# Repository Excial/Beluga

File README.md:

# Beluga
1. Created a sensor board for Beluga robotics platform
2. Contains PCB, Arduino Code

## Project description
A biosensor designed for microbial auditing, which is mounted onboard an autonomous robot as a payload. The PCB in this sensor helps to initiate helps to reduce the streamline the electronics due to space constraints to initiate the sampling sequence / processes of the biosensor.

## Design Objectives
Practice Design objectives in accordance to the IPC-2221 Standard

### V1
[✓] 3.3V LDO

[✓] 12V Buck Converter

[✓] ESP32 Module 

[✓] Bootloader

[✓] Troubleshooting LEDs

[X] Motor Driver LEDs

  - Too bright, need to increase resistance from 1K to 10K.

[✓] Motor Drivers

[X] Circuit Protection

  - Circuit Protection LED mounted wrongly, refer to schematic.
  - Source and Drain of Mosfet is mounted wrongly, needs to be switched.

[✓] M2 Mounting holes

#### Improvements
1. Add a stepper Motor driver
2. Add a buzzer
3. Add a USB Port
4. Add a FDTI chip
5. Increase Resistance for LEDs from 1k to 10K
	5a. Might Remove the LEDs altogether

### V2

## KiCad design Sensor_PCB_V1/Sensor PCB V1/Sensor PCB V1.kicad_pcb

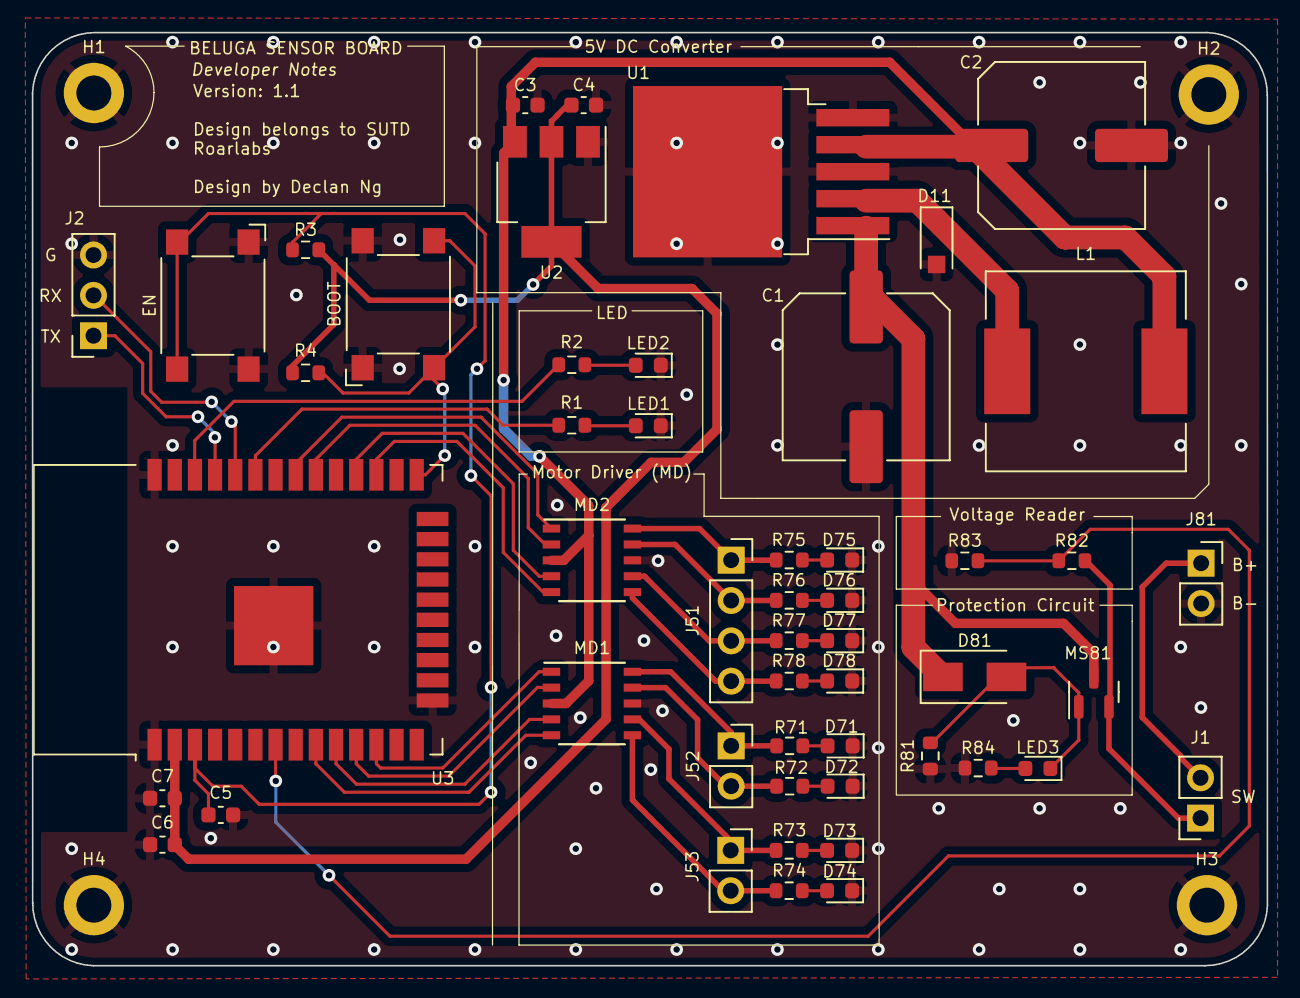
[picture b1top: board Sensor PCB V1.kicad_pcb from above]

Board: 2 copper layers, 77.8 x 58.8 mm, 55 parts (0 on the bottom side), 42 nets.

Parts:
C1: 470uF; C_Elec_10x10.2
C2: 330uF / 35V; C_Elec_10x10.2
C3, C4, C6: 22uF; C_0603_1608Metric
C5: 10uF; C_0603_1608Metric
C7: 0.1uF; C_0603_1608Metric
D11: SK32; D_SOD-123F
D71, D72, D73, D74, D75, D76, D77, D78: LED; LED_0603_1608Metric
D81: SS14; D_SMA
H1, H2, H3, H4: MountingHole_Pad; MountingHole_2.2mm_M2_DIN965_Pad
J1, J81: Conn_01x02_Male; PinSocket_1x02_P2.54mm_Vertical
J2: Conn_01x03_Male; PinSocket_1x03_P2.54mm_Vertical
J51: MD2; PinSocket_1x04_P2.54mm_Vertical
J52, J53: MD1; PinSocket_1x02_P2.54mm_Vertical
L1: 33uH / 3A; L_12x12mm_H8mm
LED1, LED2, LED3: LED; LED_0603_1608Metric
MD1, MD2: A3909; SSOP-10_3.9x4.9mm_P1.00mm
MS81: RU20P3; SOT-23
R1, R2, R3, R4, R82, R84: 1K; R_0603_1608Metric
R71, R72, R73, R74, R75, R76, R77, R78: R; R_0603_1608Metric
R81: 100K; R_0603_1608Metric
R83: 5K; R_0603_1608Metric
SW1, SW2: SW_Push; SW_SPST_Omron_B3FS-100xP
U1: LM2596S-12; TO-263-5_TabPin3
U2: AMS1117-3.3; SOT-223-3_TabPin2
U3: ESP32-WROOM-32

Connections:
3.3V: C4.1, C6.1, C7.1, R3.2, R4.2, U2.2 (VO), U3.2 (VDD)
12V: C2.1, C3.1, L1.2, MD1.3 (VBB), MD2.3 (VBB), U1.4 (FB), U2.3 (VI)
/GPIO21: R1.1, U3.33 (IO21)
/GPIO22: R2.1, U3.36 (IO22)
B+: J1.1, MS81.2 (Source), R82.1
BAT: R82.2, R83.1, U3.7 (IO35)
BOOT: R4.1, SW2.2, U3.25 (IO0)
EN: C5.2, R3.1, SW1.2, U3.3 (EN)
GND: C1.2, C2.2, C3.2, C4.2, C5.1, C6.2, C7.2, D11.2 (A), D71.1 (K), D72.1 (K), D73.1 (K), D74.1 (K), D75.1 (K), D76.1 (K), D77.1 (K), D78.1 (K), H1.1, H2.1, H3.1, H4.1, J2.3, J81.2, LED1.1 (K), LED2.1 (K), MD1.8 (GND), MD2.8 (GND), R81.1, R83.2, R84.1, SW1.1, SW2.1, U1.3 (GND), U1.5 (~ON/OFF), U2.1 (GND), U3.1 (GND), U3.15 (GND), U3.38 (GND), U3.39 (GND)
M1A: MD1.1 (IN1), U3.12 (IO27)
M1B: MD1.2 (IN2), U3.11 (IO26)
M2A: MD1.4 (IN3), U3.10 (IO25)
M2B: MD1.5 (IN4), U3.9 (IO33)
M3A: MD2.1 (IN1), U3.31 (IO19)
M3B: MD2.2 (IN2), U3.30 (IO18)
M3C: MD2.4 (IN3), U3.28 (IO17)
M3D: MD2.5 (IN4), U3.27 (IO16)
unnamed: D11.1 (K), L1.1, U1.2 (OUT)
unnamed: D71.2 (A), R71.2
unnamed: D72.2 (A), R72.2
unnamed: D73.2 (A), R73.2
unnamed: D74.2 (A), R74.2
unnamed: D75.2 (A), R75.2
unnamed: D76.2 (A), R76.2
unnamed: D77.2 (A), R77.2
unnamed: D78.2 (A), R78.2
unnamed: D81.2 (A), LED3.1 (K), MS81.1 (Gate), R81.2
unnamed: J1.2, J81.1
unnamed: LED1.2 (A), R1.2
unnamed: LED2.2 (A), R2.2
unnamed: LED3.2 (A), R84.2
O1A: J52.1, MD1.10 (OUT1), R71.1
O1B: J52.2, MD1.9 (OUT2), R72.1
O2A: J53.1, MD1.7 (OUT3), R73.1
O2B: J53.2, MD1.6 (OUT4), R74.1
O3A: J51.1, MD2.10 (OUT1), R75.1
O3B: J51.2, MD2.9 (OUT2), R76.1
O3C: J51.3, MD2.7 (OUT3), R77.1
O3D: J51.4, MD2.6 (OUT4), R78.1
RX: J2.2, U3.34 (RXD0/IO3)
TX: J2.1, U3.35 (TXD0/IO1)
VIN: C1.1, D81.1 (K), MS81.3 (Drain), U1.1 (VIN)

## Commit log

2022-08-11 Completed V1
2022-08-16 Added Code files
2022-08-16 Modified given code and called it "V2"
2022-08-16 Changed files and their directories
2022-08-16 Renamed a folder
2022-09-01 Added new folder for version 2
2022-09-03 Uploading to version1, changed schematic files
2022-09-03 Branch Edits on schematics for V2, new version1
2022-09-05 Added new Sch. files for PCB Version 2 - Circuit Protection - Added a 5V power supply - Added Circuit protection - Added additional bypass capacitors for EN - Removed troubleshooting LEDs
2022-09-05 Added untracked files not part of previous commit
2022-09-13 Updated the Biosensor PCB V2 Design Removed the DRV motor driver ICs Added a design specifications sheet
